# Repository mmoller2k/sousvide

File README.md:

# sousvide
Arduino Sous Vide PID controller.

This is a modification for running on a 2x8 LCD
with only two buttons.

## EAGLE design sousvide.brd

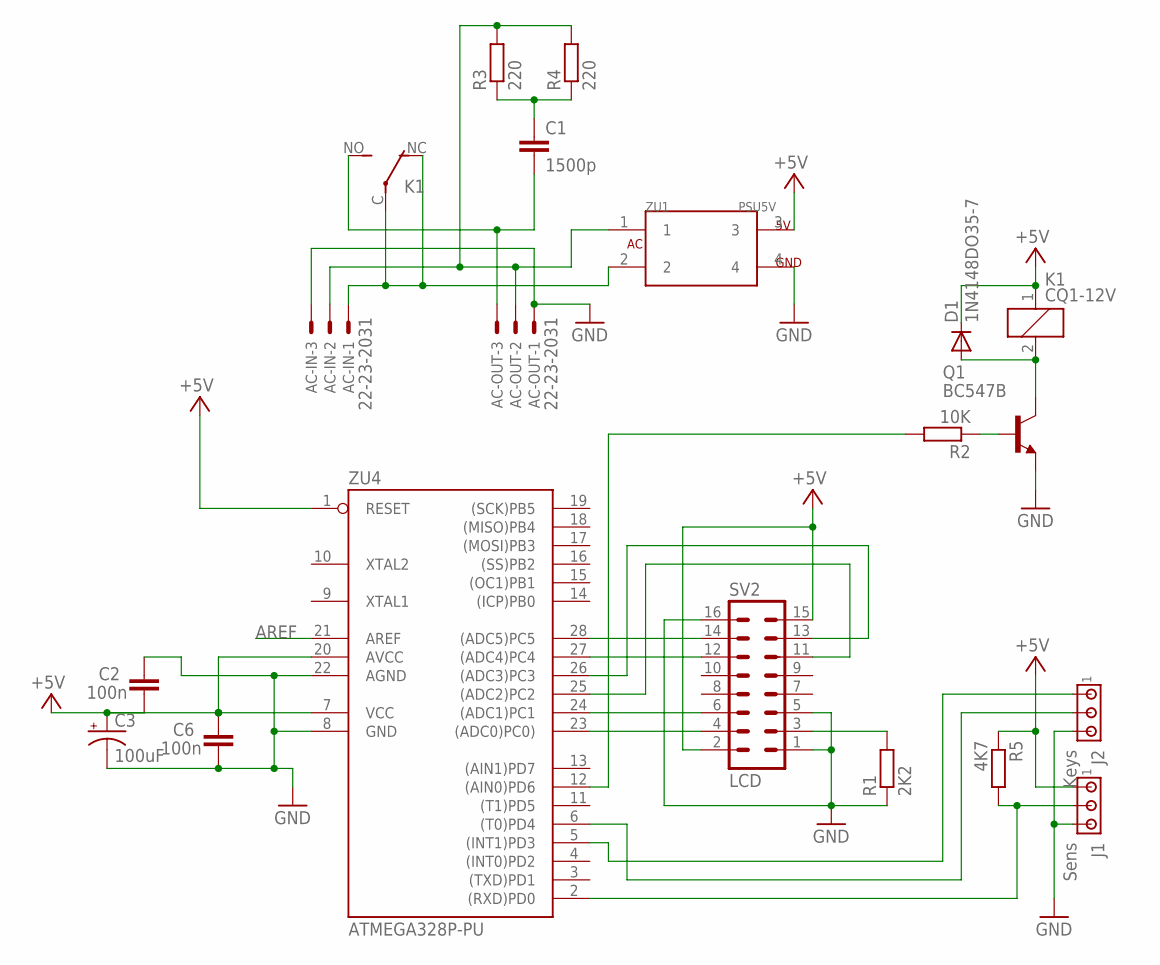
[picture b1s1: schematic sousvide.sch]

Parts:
AC-IN: 22-23-2031
AC-OUT: 22-23-2031
C1: 1500p; C7.5B4
C2, C6: 100n; C025-025X050
C3: 100uF; E2,5-5
D1: 1N4148DO35-7; DO35-7
J1: Sens; 10X03MTA
J2: Keys; 10X03MTA
K1: CQ1-12V; CQ1
Q1: BC547B; TO92
R1: 2K2; 0204/7
R2: 10K; 0204/7
R3, R4: 220; 0204/7
R5: 4K7; 0204/7
SV2: LCD; ML16
ZU1: PSU5V; USBPSU1
ZU4: ATMEGA328P-PU; DIL28-3

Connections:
+5V: C2.1, C3.+, C6.2, D1.C, J1.1, K1.1, R5.1, SV2.2, SV2.15, ZU1.3, ZU4.1 (RESET), ZU4.7 (VCC), ZU4.20 (AVCC)
AREF: ZU4.21 (AREF)
GND: AC-IN.3, AC-OUT.1, C2.2, C3.-, C6.1, J1.3, J2.3, Q1.1 (E), R1.1, SV2.1, SV2.5, SV2.16, ZU1.4, ZU4.8 (GND), ZU4.22 (AGND)
unnamed: SV2.14, ZU4.28 ((ADC5)PC5)
unnamed: SV2.12, ZU4.27 ((ADC4)PC4)
unnamed: Q1.2 (B), R2.1
unnamed: D1.A, K1.2, Q1.3 (C)
unnamed: AC-IN.1, K1.C, K1.NC (O), ZU1.2
unnamed: AC-OUT.3, C1.2, K1.NO (S)
unnamed: C1.1, R3.1, R4.1
unnamed: SV2.6, ZU4.24 ((ADC1)PC1)
unnamed: AC-IN.2, AC-OUT.2, R3.2, R4.2, ZU1.1
unnamed: SV2.4, ZU4.23 ((ADC0)PC0))
unnamed: SV2.13, ZU4.26 ((ADC3)PC3)
unnamed: SV2.11, ZU4.25 ((ADC2)PC2)
unnamed: J1.2, R5.2, ZU4.2 ((RXD)PD0)
unnamed: J2.2, ZU4.6 ((T0)PD4)
unnamed: J2.1, ZU4.5 ((INT1)PD3)
unnamed: R1.2, SV2.3
unnamed: R2.2, ZU4.12 ((AIN0)PD6)

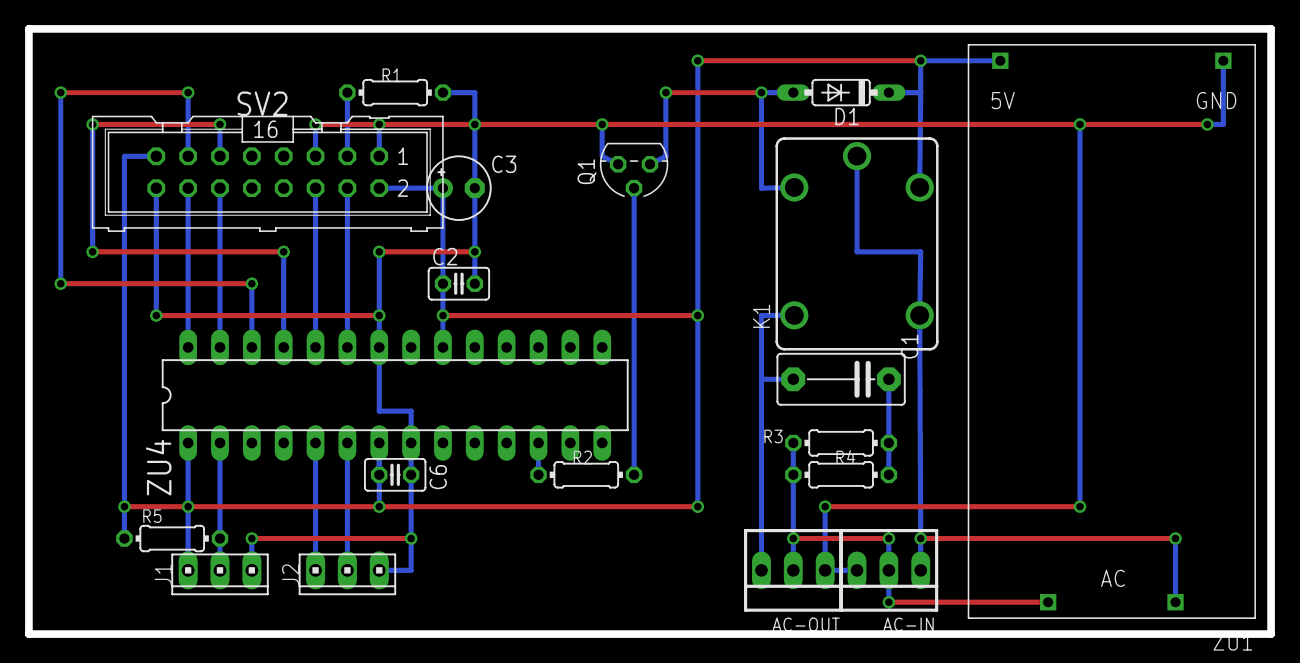
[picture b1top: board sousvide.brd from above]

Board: 2 copper layers, 99.1 x 48.3 mm, 19 parts (0 on the bottom side), 19 nets.

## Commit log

2016-06-12 Fixed relay timing, moved pins
2016-08-30 Added start delay timer
